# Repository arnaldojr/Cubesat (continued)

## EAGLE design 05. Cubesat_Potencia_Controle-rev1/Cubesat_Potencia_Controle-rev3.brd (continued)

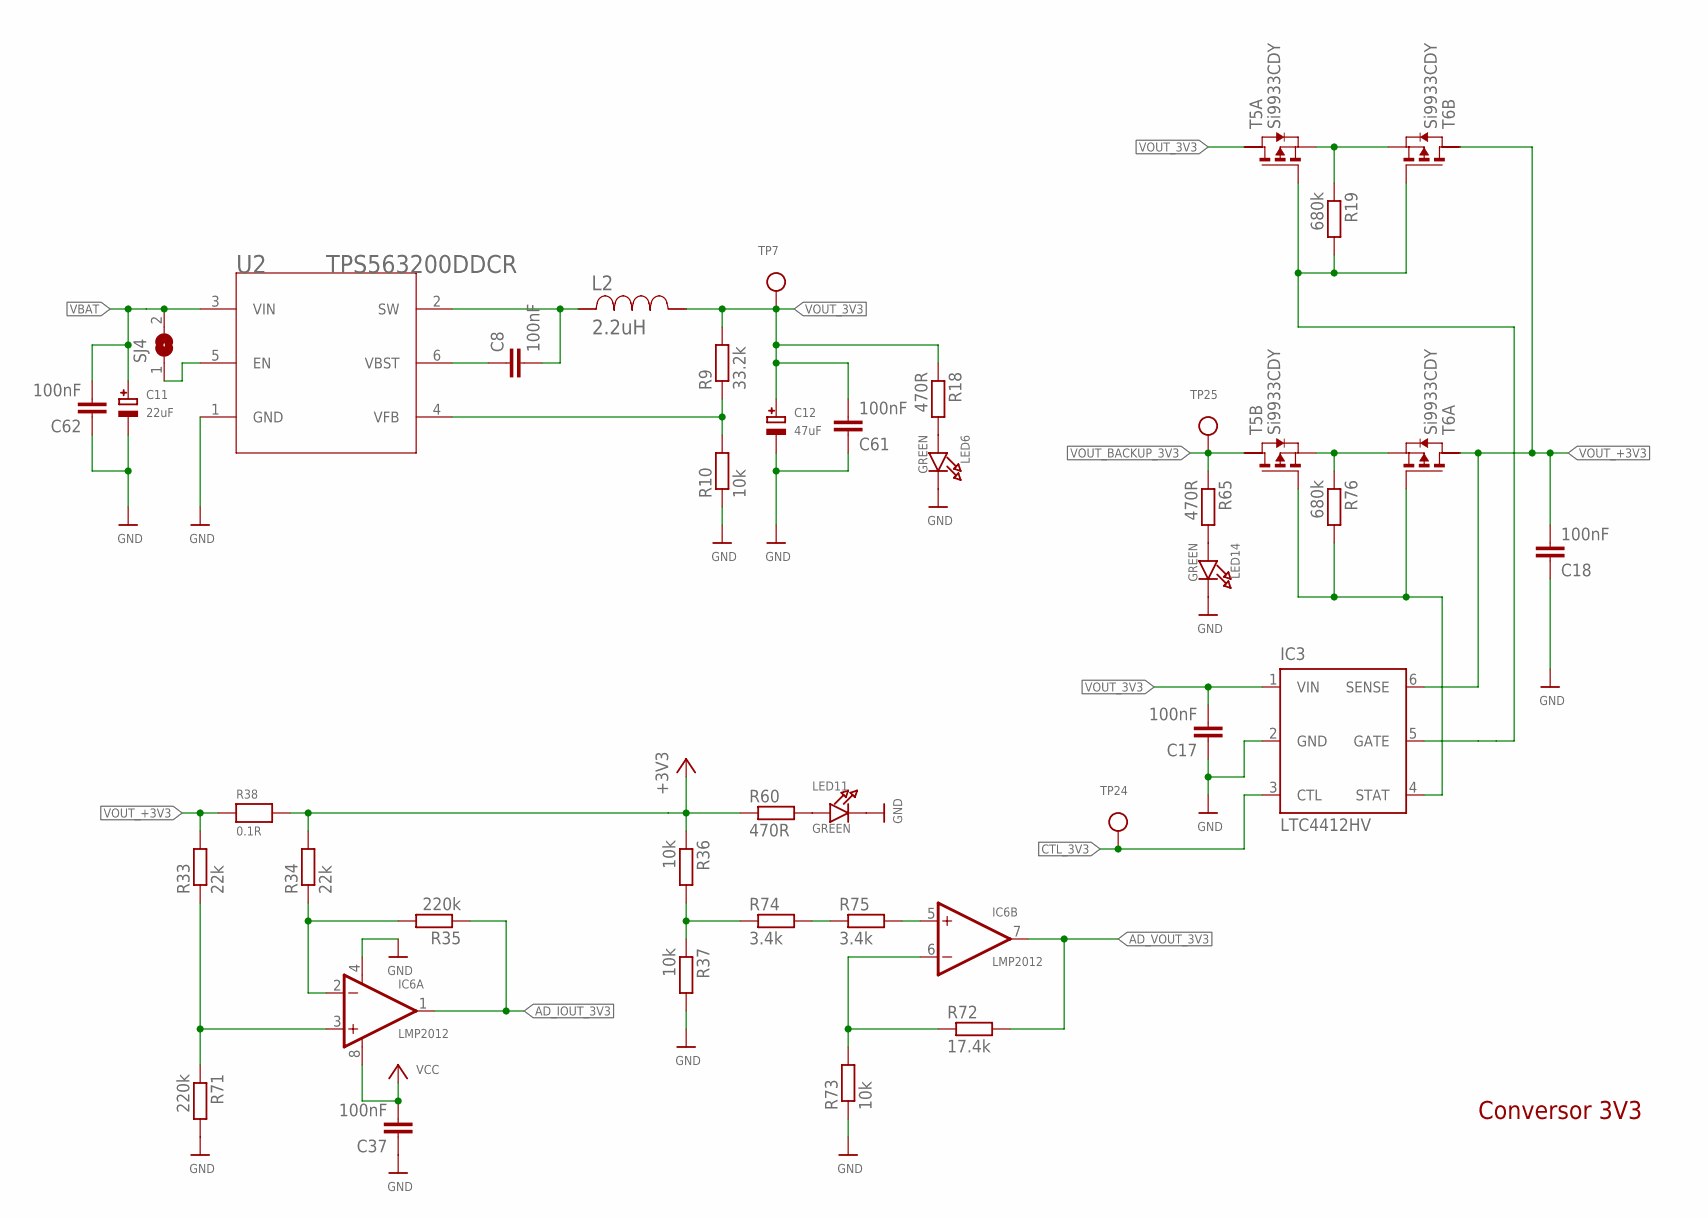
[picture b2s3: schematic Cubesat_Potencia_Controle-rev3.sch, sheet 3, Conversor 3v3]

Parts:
C8, C17, C18, C37, C61, C62: 100nF; C0805
C11: 22uF; EIA6032-28/C-R
C12: 47uF; EIA6032-28/C-R
IC3: LTC4412HV; TSOT23-6
IC6: LMP2012; MSOP08; MPN OPA2237EA/250
L2: 2.2uH; SRR6038
LED6, LED11, LED14: GREEN; CHIPLED_0805
R9: 33.2k; M0805
R10, R36, R37, R73: 10k; M0805
R18, R60, R65: 470R; M0805
R19, R76: 680k; M0805
R33, R34: 22k; M0805
R35, R71: 220k; M0805
R38: 0.1R; _2818
R72: 17.4k; M0805
R74, R75: 3.4k; M0805
SJ4: SOLDERJUMPER; SOLDERJUMPER_ARROW_NOPASTE
T5, T6: Si9933CDY; SO8
TP7, TP24, TP25: TESTPOINT0.1"; 1X01_ROUND
U2: TPS563200DDCR; DDC0006A

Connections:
+3V3: R34.2, R36.1, R38.2, R60.1; also elsewhere on the board
AD_IOUT_3V3: IC6.1 (OUT), R35.1; also elsewhere on the board
AD_VOUT_3V3: IC6.7 (OUT), R72.2; also elsewhere on the board
CTL_3V3: IC3.3 (CTL), TP24.1; also elsewhere on the board
GND: C11.-, C12.-, C17.1, C18.1, C37.1, C61.1, C62.1, IC3.2 (GND), IC6.4 (V-), LED6.C, LED11.C, LED14.C, R10.1, R37.2, R71.2, R73.1, U2.1 (GND); also elsewhere on the board
unnamed: C8.1, U2.6 (VBST)
unnamed: C8.2, L2.1, U2.2 (SW)
unnamed: R9.1, R10.2, U2.4 (VFB)
unnamed: IC6.6 (-IN), R72.1, R73.2
unnamed: R74.2, R75.1
unnamed: R19.1, T5.1 (S), T6.3 (S)
unnamed: R76.1, T5.3 (S), T6.1 (S)
unnamed: IC3.4 (STAT), R76.2, T5.4 (G), T6.2 (G)
unnamed: IC6.5 (+IN), R75.2
unnamed: LED6.A, R18.2
unnamed: R36.2, R37.1, R74.1
unnamed: IC6.2 (-IN), R34.1, R35.2
unnamed: IC6.3 (+IN), R33.1, R71.1
unnamed: LED11.A, R60.2
unnamed: LED14.A, R65.2
unnamed: SJ4.1, U2.5 (EN)
STAT_3V3: IC3.5 (GATE), R19.2, T5.2 (G), T6.4 (G)
VBAT: C11.+, C62.2, SJ4.2, U2.3 (VIN); also elsewhere on the board
VCC: C37.2, IC6.8 (V+); also elsewhere on the board
VOUT_3V3: C12.+, C17.2, C61.2, IC3.1 (VIN), L2.2, R9.2, R18.1, T5.7 (D), TP7.1
VOUT_+3V3: C18.2, IC3.6 (SENSE), R33.2, R38.1, T6.6 (D), T6.7 (D)
VOUT_BACKUP_3V3: R65.1, T5.6 (D), TP25.1; also elsewhere on the board

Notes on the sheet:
Conversor 3V3

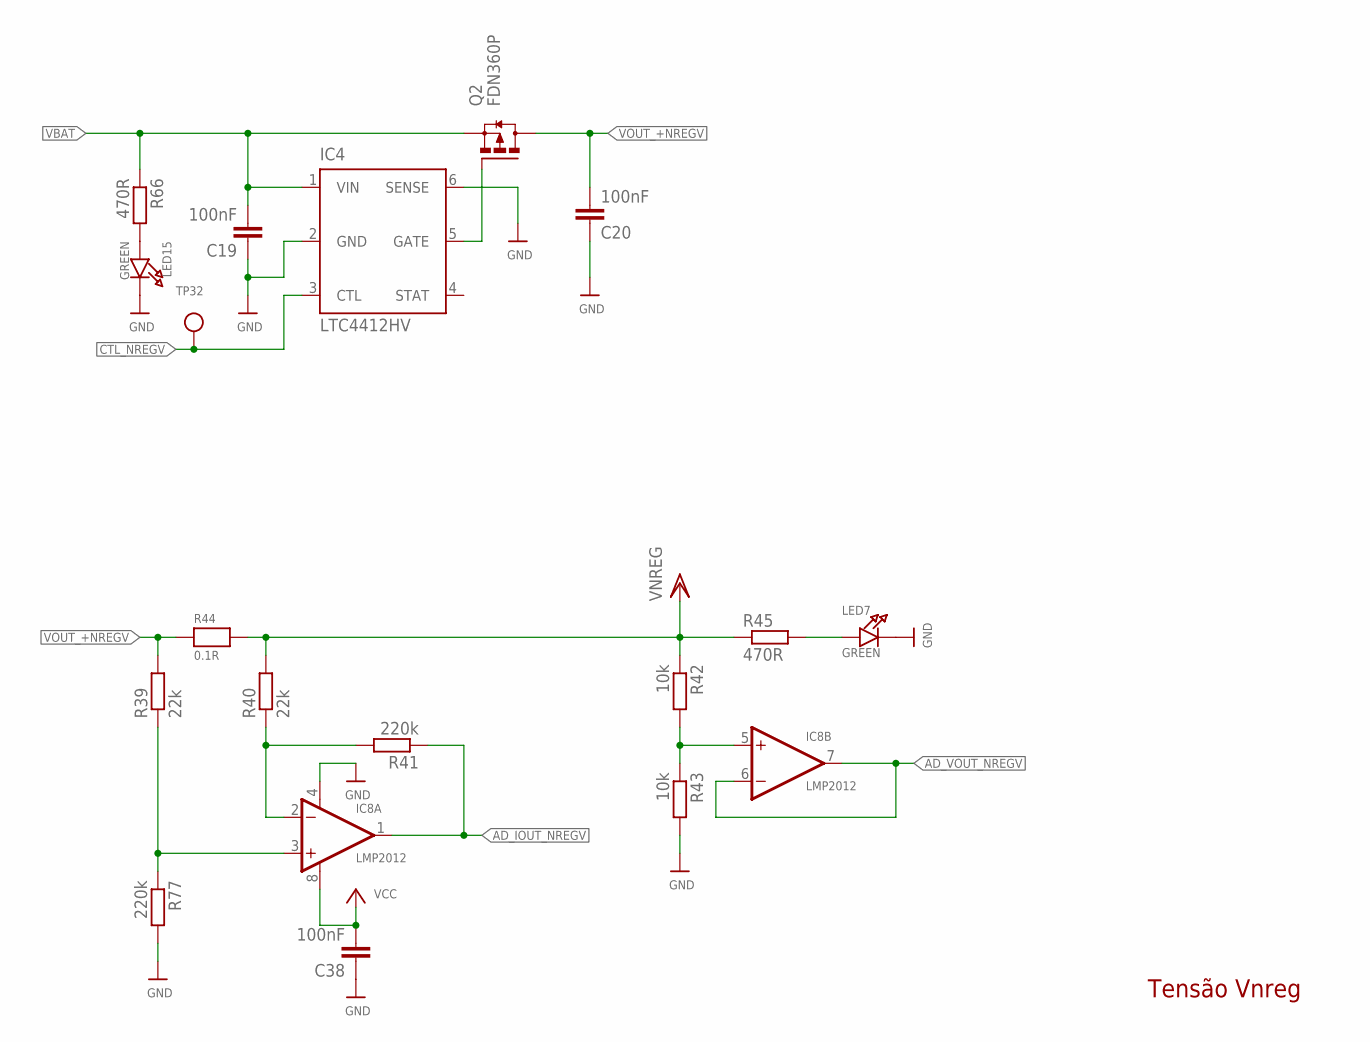
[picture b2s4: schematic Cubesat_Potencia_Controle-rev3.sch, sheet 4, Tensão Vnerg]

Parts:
C19, C20, C38: 100nF; C0805
IC4: LTC4412HV; TSOT23-6
IC8: LMP2012; MSOP08; MPN OPA2237EA/250
LED7, LED15: GREEN; CHIPLED_0805
Q2: FDN360P; SUPER-SOT3
R39, R40: 22k; M0805
R41, R77: 220k; M0805
R42, R43: 10k; M0805
R44: 0.1R; _2818
R45, R66: 470R; M0805
TP32: TESTPOINT0.1"; 1X01_ROUND

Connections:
AD_IOUT_NREGV: IC8.1 (OUT), R41.1; also elsewhere on the board
AD_VOUT_NREGV: IC8.6 (-IN), IC8.7 (OUT); also elsewhere on the board
CTL_NREGV: IC4.3 (CTL), TP32.1; also elsewhere on the board
GND: C19.1, C20.1, C38.1, IC4.2 (GND), IC4.6 (SENSE), IC8.4 (V-), LED7.C, LED15.C, R43.2, R77.2; also elsewhere on the board
unnamed: IC4.5 (GATE), Q2.1 (G)
unnamed: IC8.5 (+IN), R42.2, R43.1
unnamed: IC8.2 (-IN), R40.1, R41.2
unnamed: IC8.3 (+IN), R39.1, R77.1
unnamed: LED7.A, R45.2
unnamed: LED15.A, R66.2
VBAT: C19.2, IC4.1 (VIN), Q2.2 (S), R66.1; also elsewhere on the board
VCC: C38.2, IC8.8 (V+); also elsewhere on the board
VNREG: R40.2, R42.1, R44.2, R45.1; also elsewhere on the board
VOUT_+NREGV: C20.2, Q2.3 (D), R39.2, R44.1

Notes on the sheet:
Tensão Vnreg

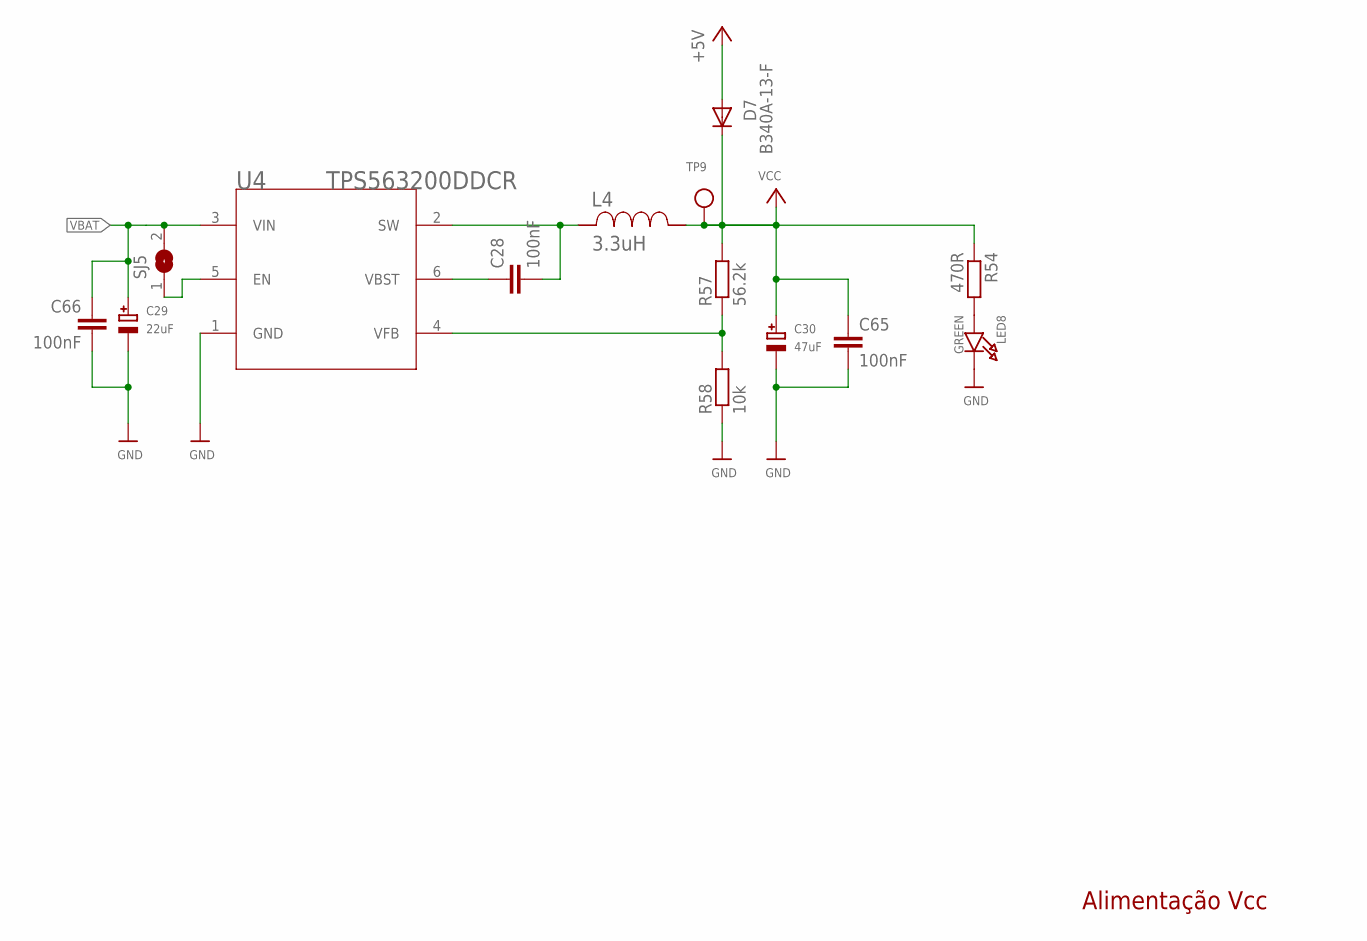
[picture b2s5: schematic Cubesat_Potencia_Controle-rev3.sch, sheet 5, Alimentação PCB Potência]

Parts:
C28, C65, C66: 100nF; C0805
C29: 22uF; EIA6032-28/C-R
C30: 47uF; EIA6032-28/C-R
D7: B340A-13-F; DO214AC
L4: 3.3uH; SRR6038
LED8: GREEN; CHIPLED_0805
R54: 470R; M0805
R57: 56.2k; M0805
R58: 10k; M0805
SJ5: SOLDERJUMPER; SOLDERJUMPER_ARROW_NOPASTE
TP9: TESTPOINT0.1"; 1X01_ROUND
U4: TPS563200DDCR; DDC0006A

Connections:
+5V: D7.A; also elsewhere on the board
GND: C29.-, C30.-, C65.2, C66.2, LED8.C, R58.1, U4.1 (GND); also elsewhere on the board
unnamed: C28.1, U4.6 (VBST)
unnamed: C28.2, L4.1, U4.2 (SW)
unnamed: R57.1, R58.2, U4.4 (VFB)
unnamed: LED8.A, R54.2
unnamed: SJ5.1, U4.5 (EN)
VBAT: C29.+, C66.1, SJ5.2, U4.3 (VIN); also elsewhere on the board
VCC: C30.+, C65.1, D7.C, L4.2, R54.1, R57.2, TP9.1; also elsewhere on the board

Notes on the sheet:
Alimentação Vcc

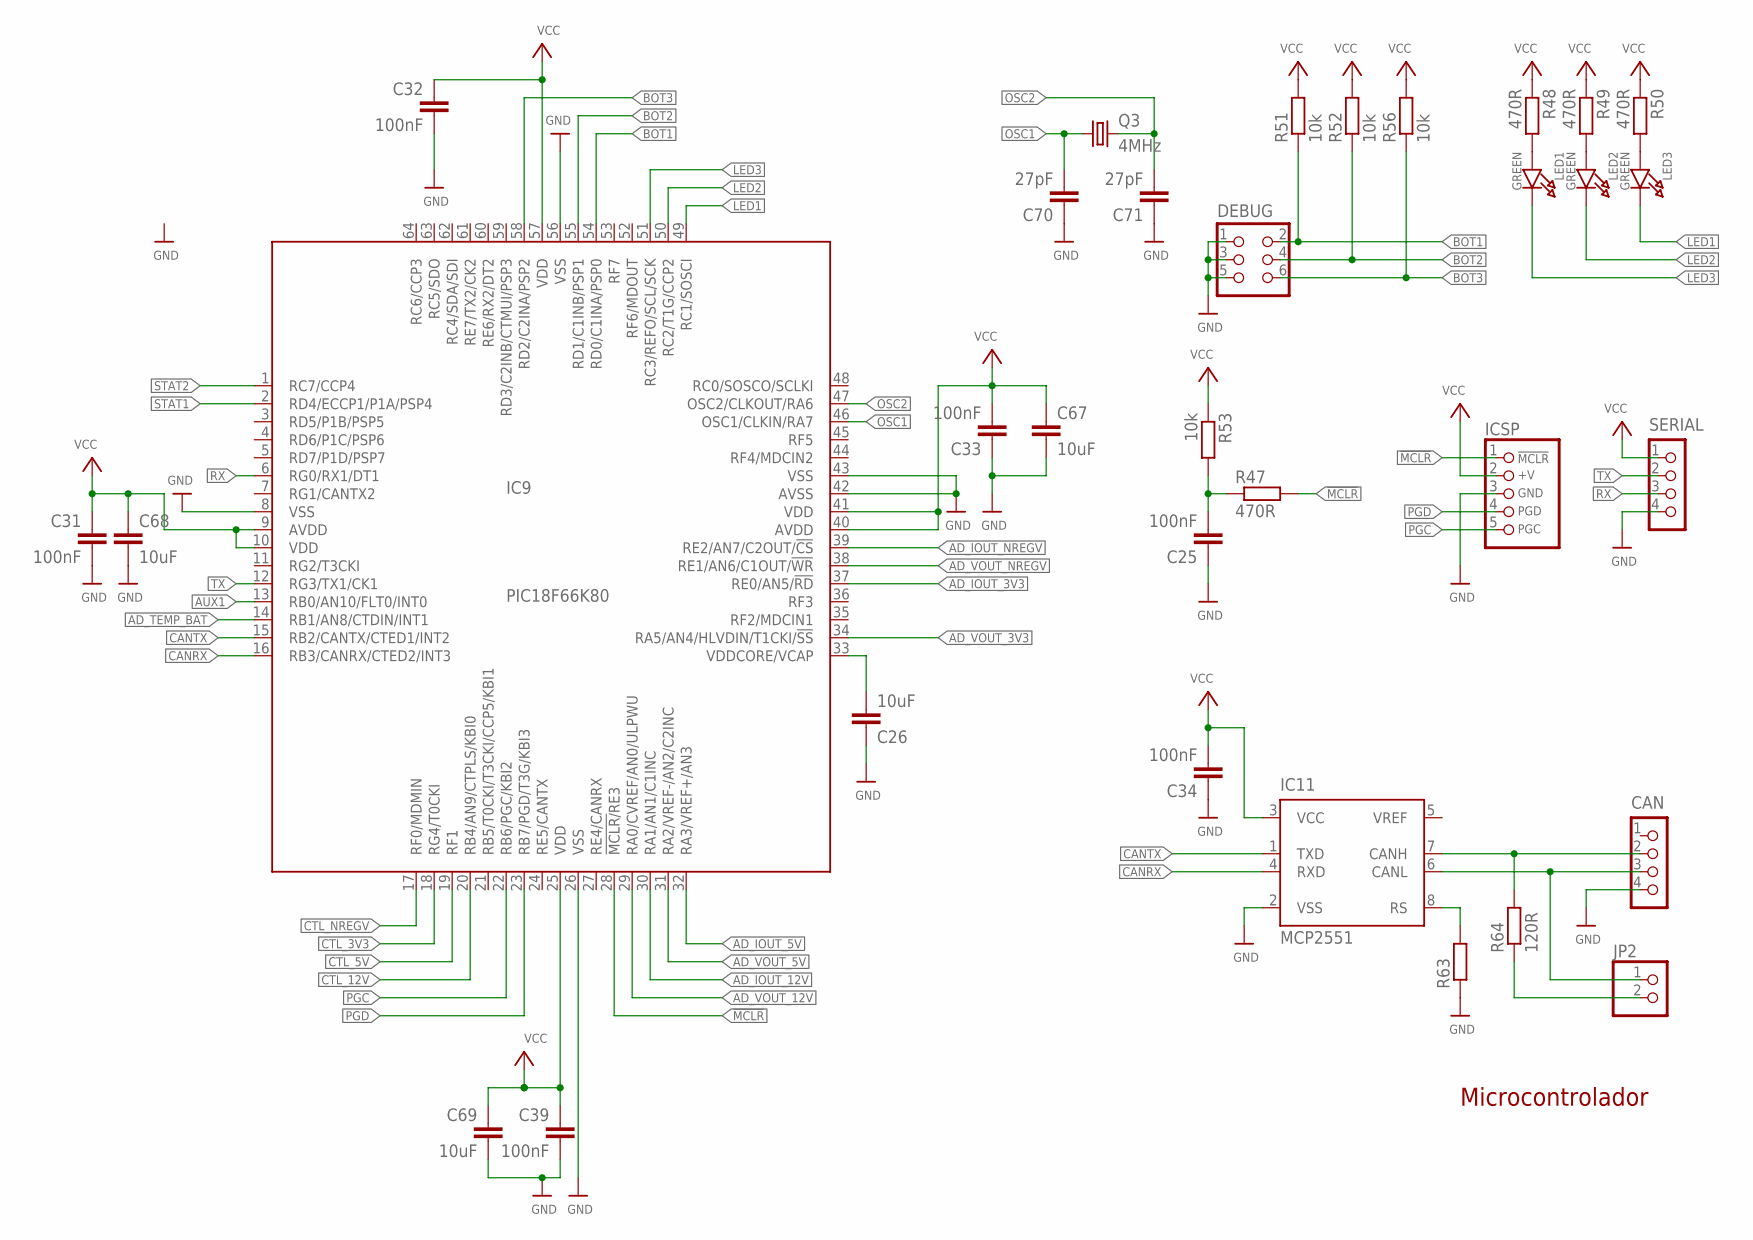
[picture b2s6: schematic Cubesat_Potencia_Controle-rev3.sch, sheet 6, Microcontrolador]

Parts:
C25, C31, C32, C33, C34, C39: 100nF; C0805
C26, C67, C68, C69: 10uF; C0805
C70, C71: 27pF; C0805
CAN: CON_HEADER_1X04; M1X4
DEBUG: CON_HEADER_2X03-PTH; M2X3
IC9: PIC18F66K80; TQFP64-10X10X1MM
IC11: MCP2551; SO-08
ICSP: CON_HEADER_PRG_PIC_ICSP0.1INCH_B; HEADER_PRG_1X05_ICSP_B
JP2: HEADER-1X2ROUND; 1X02_ROUND
LED1, LED2, LED3: GREEN; CHIPLED_0805
Q3: 4MHz; HC49/S
R47, R48, R49, R50: 470R; M0805
R51, R52, R53, R56: 10k; M0805
R63: R-EU_M0805; M0805
R64: 120R; M0805
SERIAL: CON_HEADER_1X04; M1X4

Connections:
!MCLR: IC9.28 (!MCLR/!RE3), ICSP.1 (/MCLR), R47.2
AD_IOUT_3V3: IC9.37 (RE0/AN5/!RD); also elsewhere on the board
AD_IOUT_5V: IC9.32 (RA3/VREF+/AN3); also elsewhere on the board
AD_IOUT_12V: IC9.30 (RA1/AN1/C1INC); also elsewhere on the board
AD_IOUT_NREGV: IC9.39 (RE2/AN7/C2OUT/!CS); also elsewhere on the board
AD_TEMP_BAT: IC9.14 (RB1/AN8/CTDIN/INT1); also elsewhere on the board
AD_VOUT_3V3: IC9.34 (RA5/AN4/HLVDIN/T1CKI/!SS); also elsewhere on the board
AD_VOUT_5V: IC9.31 (RA2/VREF-/AN2/C2INC); also elsewhere on the board
AD_VOUT_12V: IC9.29 (RA0/CVREF/AN0/ULPWU); also elsewhere on the board
AD_VOUT_NREGV: IC9.38 (RE1/AN6/C1OUT/!WR); also elsewhere on the board
AUX1: IC9.13 (RB0/AN10/FLT0/INT0); also elsewhere on the board
BOT1: DEBUG.2, IC9.54 (RD0/C1INA/PSP0), R51.1
BOT2: DEBUG.4, IC9.55 (RD1/C1INB/PSP1), R52.1
BOT3: DEBUG.6, IC9.58 (RD2/C2INA/PSP2), R56.1
CANRX: IC9.16 (RB3/CANRX/CTED2/INT3), IC11.4 (RXD)
CANTX: IC9.15 (RB2/CANTX/CTED1/INT2), IC11.1 (TXD)
CTL_3V3: IC9.18 (RG4/T0CKI); also elsewhere on the board
CTL_5V: IC9.19 (RF1); also elsewhere on the board
CTL_12V: IC9.20 (RB4/AN9/CTPLS/KBI0); also elsewhere on the board
CTL_NREGV: IC9.17 (RF0/MDMIN); also elsewhere on the board
GND: C25.1, C26.1, C31.2, C32.2, C33.1, C34.1, C39.2, C67.2, C68.2, C69.2, C70.1, C71.1, CAN.4, DEBUG.1, DEBUG.3, DEBUG.5, IC9.8 (VSS), IC9.26 (VSS), IC9.42 (AVSS), IC9.43 (VSS), IC9.56 (VSS), IC11.2 (VSS), ICSP.3 (GND), R63.1, SERIAL.4; also elsewhere on the board
LED1: IC9.49 (RC1/SOSCI), LED3.C
LED2: IC9.50 (RC2/T1G/CCP2), LED2.C
LED3: IC9.51 (RC3/REFO/SCL/SCK), LED1.C
unnamed: LED1.A, R48.2
unnamed: LED2.A, R49.2
unnamed: LED3.A, R50.2
unnamed: C25.2, R47.1, R53.2
unnamed: C26.2, IC9.33 (VDDCORE/VCAP)
unnamed: JP2.2, R64.1
unnamed: CAN.2, IC11.7 (CANH), R64.2
unnamed: CAN.3, IC11.6 (CANL), JP2.1
unnamed: IC11.8 (RS), R63.2
OSC1: C70.2, IC9.46 (OSC1/CLKIN/RA7), Q3.1
OSC2: C71.2, IC9.47 (OSC2/CLKOUT/RA6), Q3.2
PGC: IC9.22 (RB6/PGC/KBI2), ICSP.5 (PGC)
PGD: IC9.23 (RB7/PGD/T3G/KBI3), ICSP.4 (PGD)
RX: IC9.6 (RG0/RX1/DT1), SERIAL.3
STAT1: IC9.2 (RD4/ECCP1/P1A/PSP4); also elsewhere on the board
STAT2: IC9.1 (RC7/CCP4); also elsewhere on the board
TX: IC9.12 (RG3/TX1/CK1), SERIAL.2
VCC: C31.1, C32.1, C33.2, C34.2, C39.1, C67.1, C68.1, C69.1, IC9.9 (AVDD), IC9.10 (VDD), IC9.25 (VDD), IC9.40 (AVDD), IC9.41 (VDD), IC9.57 (VDD), IC11.3 (VCC), ICSP.2 (+V), R48.1, R49.1, R50.1, R51.2, R52.2, R53.1, R56.2, SERIAL.1; also elsewhere on the board

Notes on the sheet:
Microcontrolador

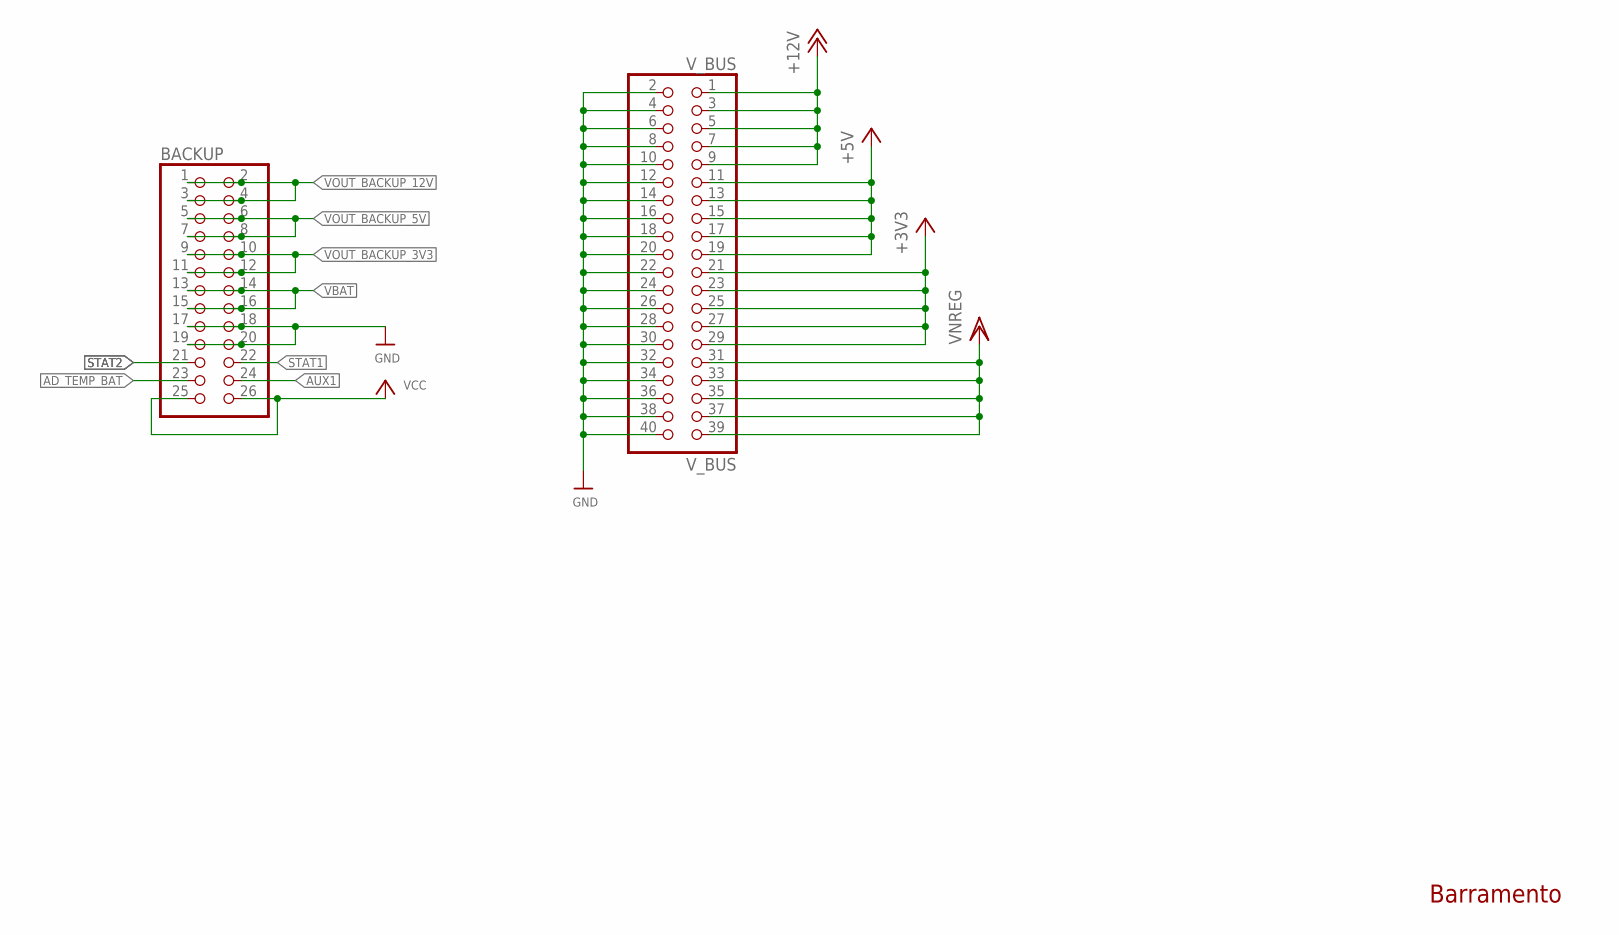
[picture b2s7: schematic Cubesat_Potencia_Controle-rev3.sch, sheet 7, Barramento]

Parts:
BACKUP: HEADER-2X13; 2X13
V_BUS: V_BUS; 2X20

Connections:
+3V3: V_BUS.21, V_BUS.23, V_BUS.25, V_BUS.27, V_BUS.29; also elsewhere on the board
+5V: V_BUS.11, V_BUS.13, V_BUS.15, V_BUS.17, V_BUS.19; also elsewhere on the board
+12V: V_BUS.1, V_BUS.3, V_BUS.5, V_BUS.7, V_BUS.9; also elsewhere on the board
AD_TEMP_BAT: BACKUP.23; also elsewhere on the board
AUX1: BACKUP.24; also elsewhere on the board
GND: BACKUP.17, BACKUP.18, BACKUP.19, BACKUP.20, V_BUS.2, V_BUS.4, V_BUS.6, V_BUS.8, V_BUS.10, V_BUS.12, V_BUS.14, V_BUS.16, V_BUS.18, V_BUS.20, V_BUS.22, V_BUS.24, V_BUS.26, V_BUS.28, V_BUS.30, V_BUS.32, V_BUS.34, V_BUS.36, V_BUS.38, V_BUS.40; also elsewhere on the board
STAT1: BACKUP.22; also elsewhere on the board
STAT2: BACKUP.21; also elsewhere on the board
VBAT: BACKUP.13, BACKUP.14, BACKUP.15, BACKUP.16; also elsewhere on the board
VCC: BACKUP.25, BACKUP.26; also elsewhere on the board
VNREG: V_BUS.31, V_BUS.33, V_BUS.35, V_BUS.37, V_BUS.39; also elsewhere on the board
VOUT_BACKUP_3V3: BACKUP.9, BACKUP.10, BACKUP.11, BACKUP.12; also elsewhere on the board
VOUT_BACKUP_5V: BACKUP.5, BACKUP.6, BACKUP.7, BACKUP.8; also elsewhere on the board
VOUT_BACKUP_12V: BACKUP.1, BACKUP.2, BACKUP.3, BACKUP.4; also elsewhere on the board

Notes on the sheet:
Barramento

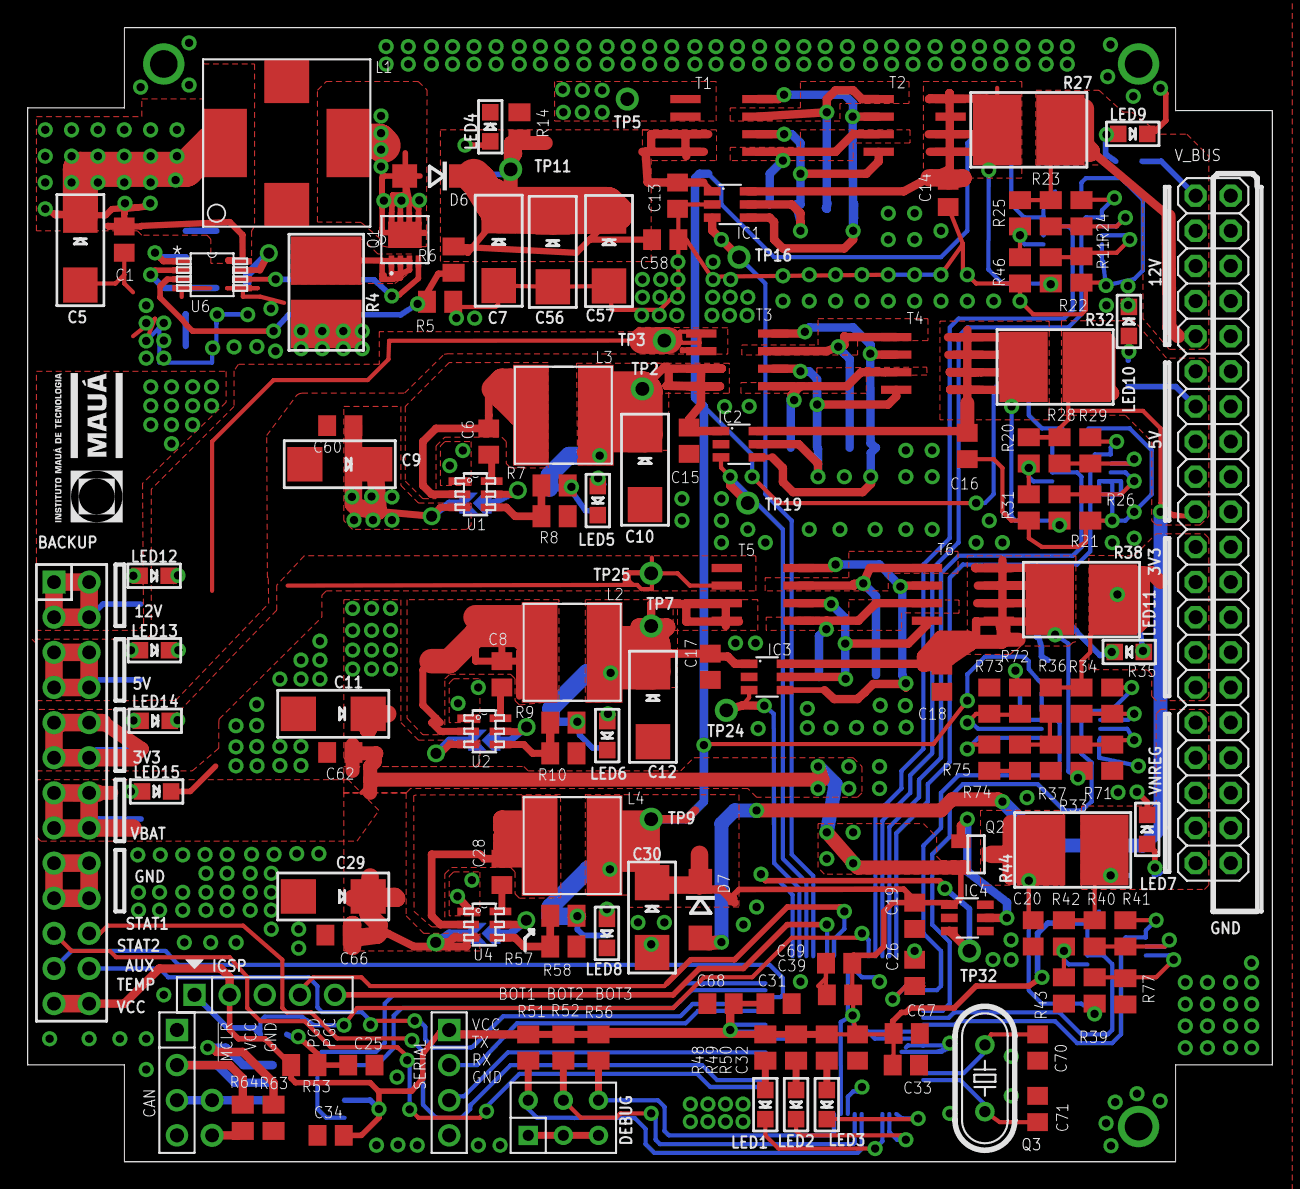
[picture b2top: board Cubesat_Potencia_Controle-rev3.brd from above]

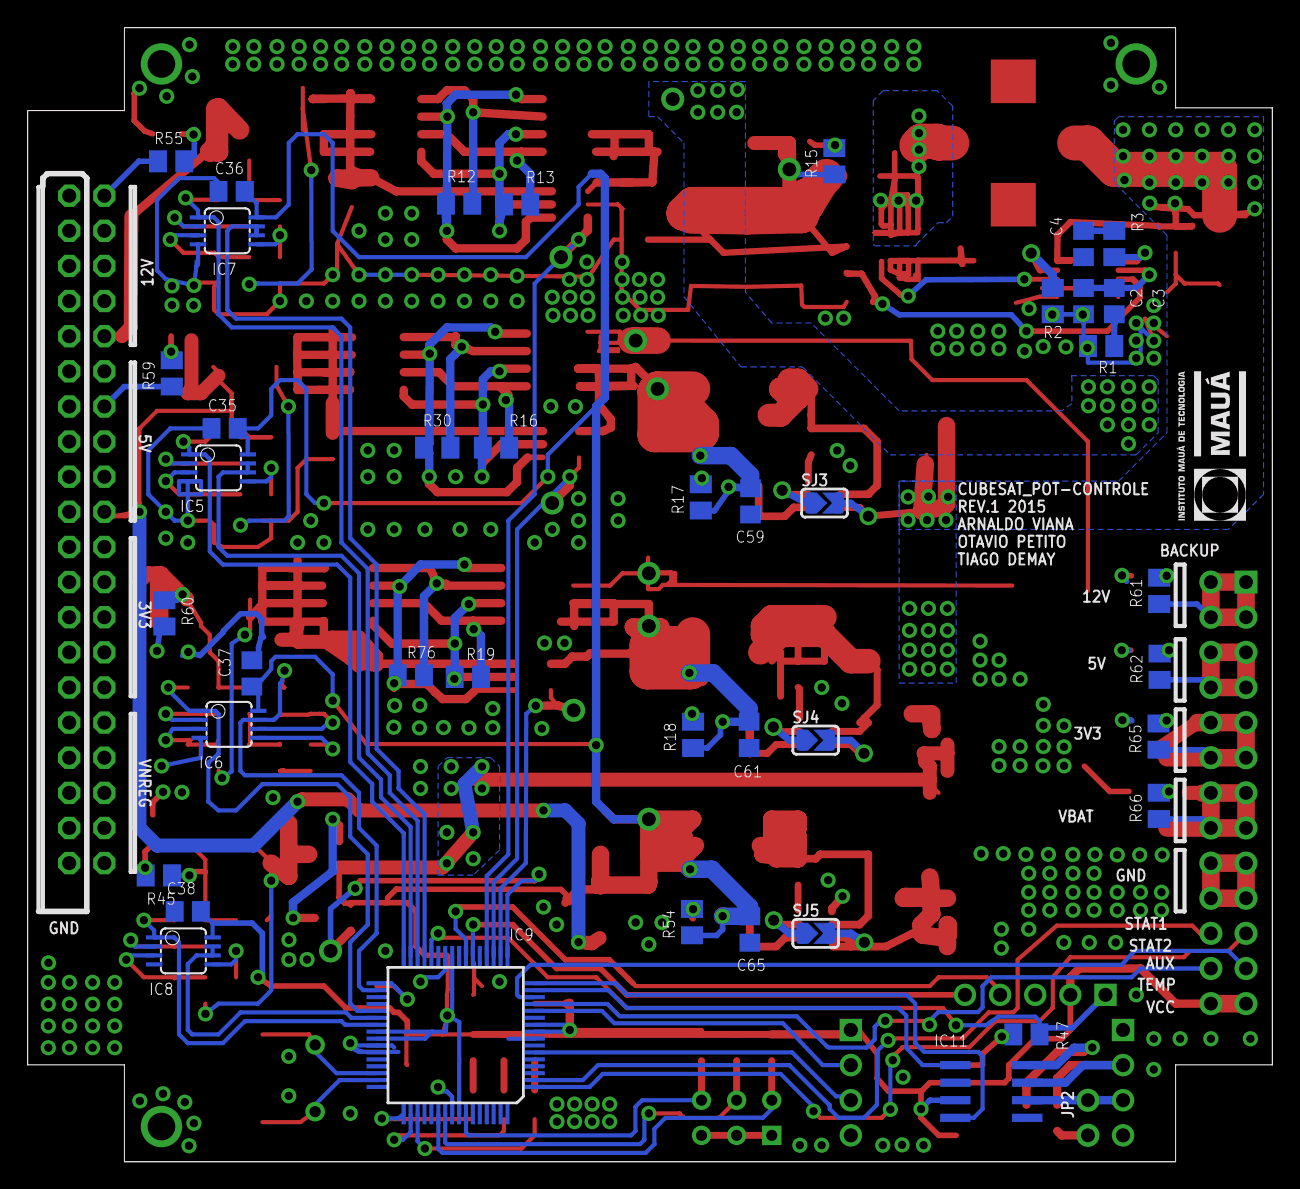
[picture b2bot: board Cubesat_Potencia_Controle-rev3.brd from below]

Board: 2 copper layers, 90.0 x 82.0 mm, 188 parts (43 on the bottom side), 118 nets.

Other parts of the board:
U$112, U$113: LOGO_MAUA

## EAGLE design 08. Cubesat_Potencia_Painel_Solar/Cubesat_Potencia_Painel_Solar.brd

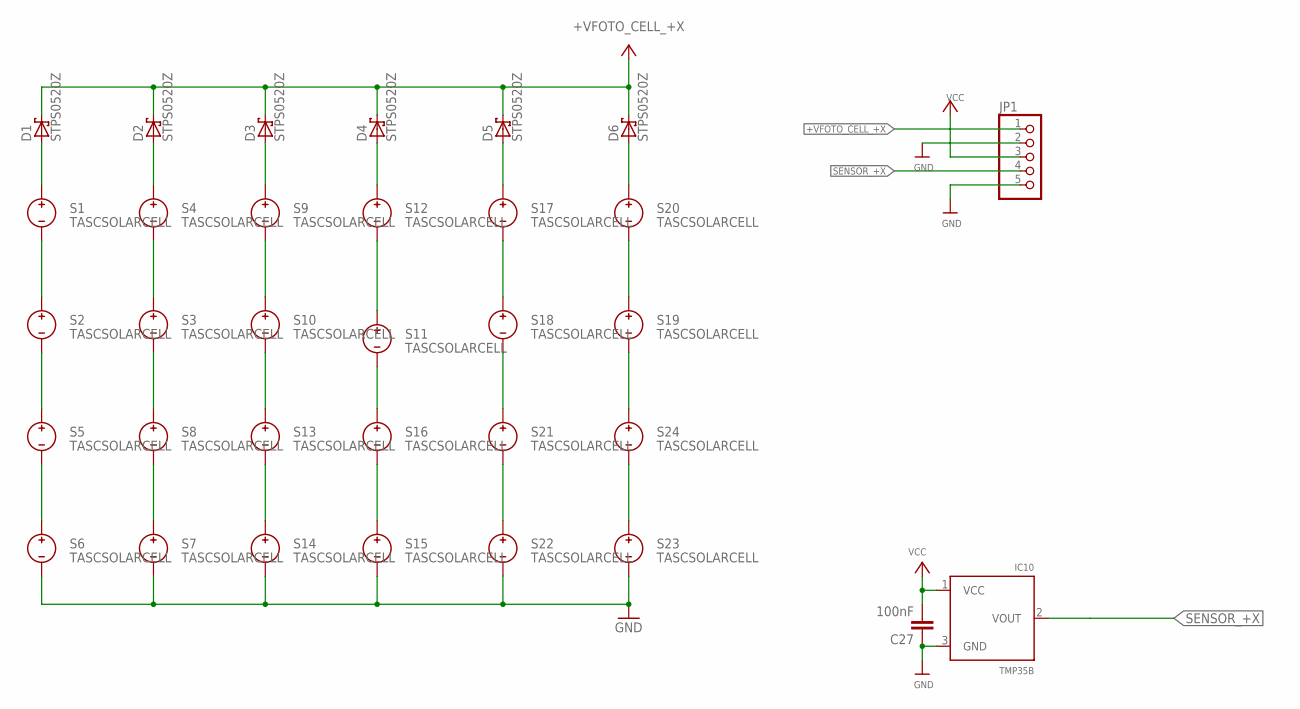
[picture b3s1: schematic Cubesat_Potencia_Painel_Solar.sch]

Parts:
C27: 100nF; C0805
D1, D2, D3, D4, D5, D6: STPS0520Z; SOD-123
IC10: TMP35B; TO92-LINE
JP1: HEADER-1X5SMT; 1X05_SMT
S1, S2, S3, S4, S5, S6, S7, S8, S9, S10, S11, S12, S13, S14, S15, S16, S17, S18, S19, S20, S21, S22, S23, S24: TASCSOLARCELL

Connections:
+VFOTO_CELL_+X: D1.C, D2.C, D3.C, D4.C, D5.C, D6.C, JP1.1
GND: C27.1, IC10.3 (GND), JP1.2, JP1.5, S6.N, S7.N, S14.N, S15.N, S22.N, S23.N
unnamed: D1.A, S1.P
unnamed: S1.N, S2.P
unnamed: S2.N, S5.P
unnamed: S5.N, S6.P
unnamed: S7.P, S8.N
unnamed: S3.N, S8.P
unnamed: S3.P, S4.N
unnamed: S13.N, S14.P
unnamed: S10.N, S13.P
unnamed: S9.N, S10.P
unnamed: S15.P, S16.N
unnamed: S11.N, S16.P
unnamed: S11.P, S12.N
unnamed: S21.N, S22.P
unnamed: S18.N, S21.P
unnamed: S17.N, S18.P
unnamed: S23.P, S24.N
unnamed: S19.N, S24.P
unnamed: S19.P, S20.N
unnamed: D2.A, S4.P
unnamed: D3.A, S9.P
unnamed: D4.A, S12.P
unnamed: D5.A, S17.P
unnamed: D6.A, S20.P
SENSOR_+X: IC10.2 (VOUT), JP1.4
VCC: C27.2, IC10.1 (VCC), JP1.3

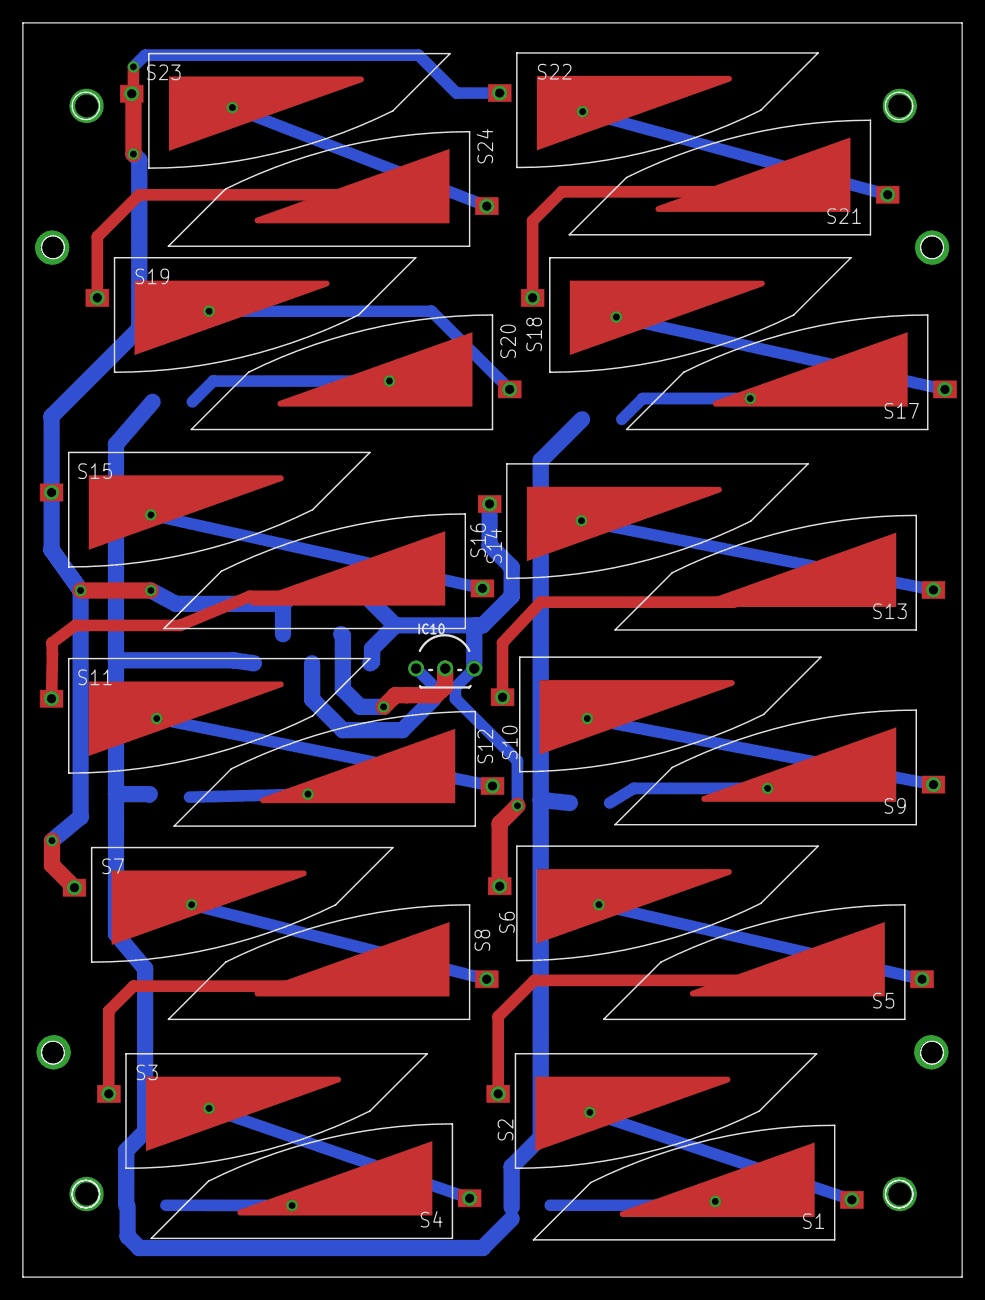
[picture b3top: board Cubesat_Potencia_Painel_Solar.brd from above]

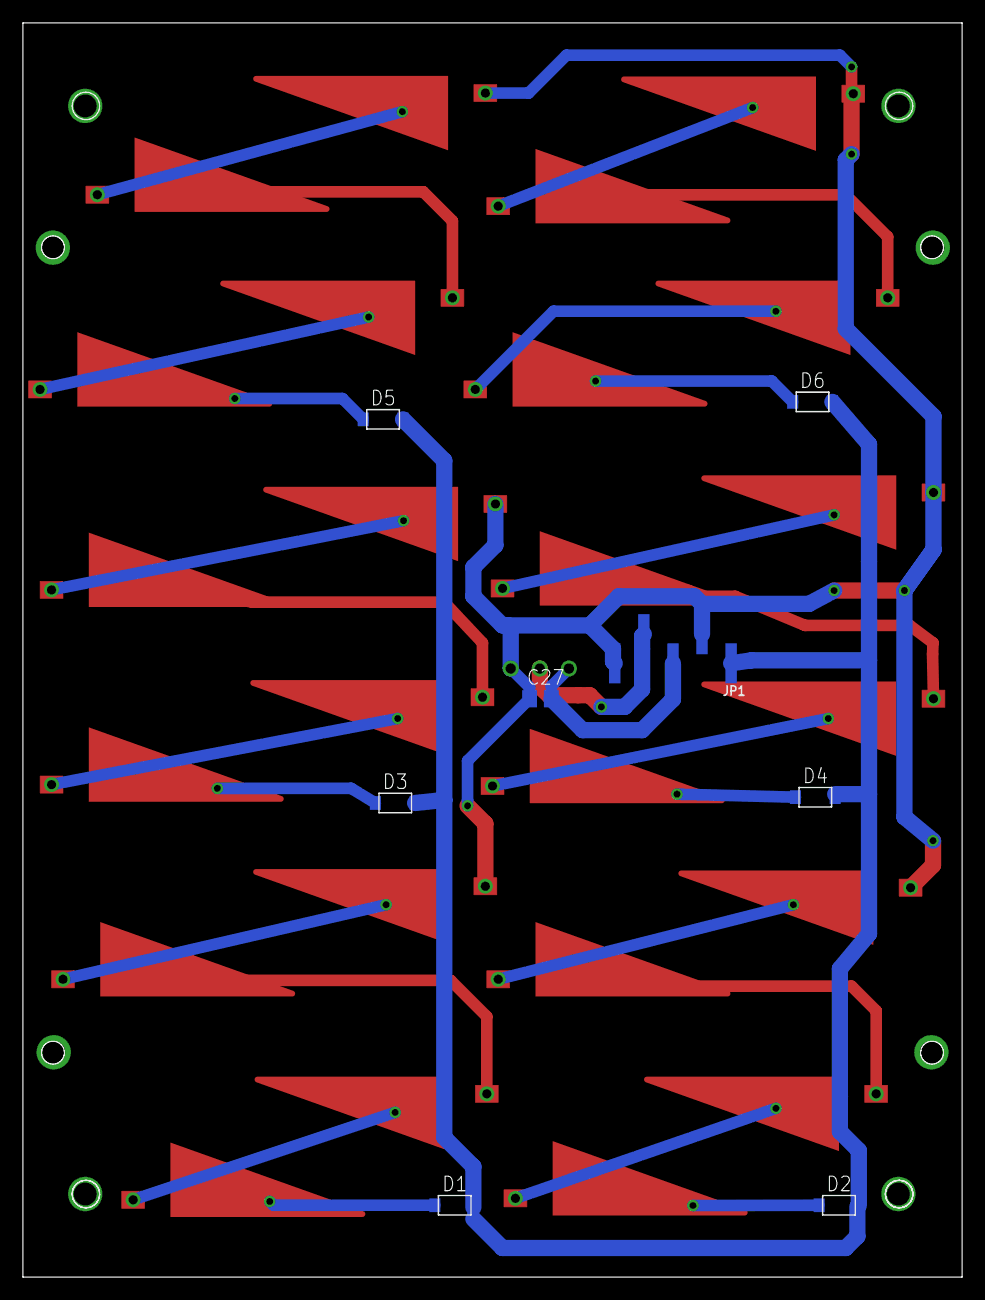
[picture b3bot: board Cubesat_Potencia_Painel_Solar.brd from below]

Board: 2 copper layers, 82.0 x 109.5 mm, 33 parts (8 on the bottom side), 28 nets.

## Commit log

2018-11-02 init commit
